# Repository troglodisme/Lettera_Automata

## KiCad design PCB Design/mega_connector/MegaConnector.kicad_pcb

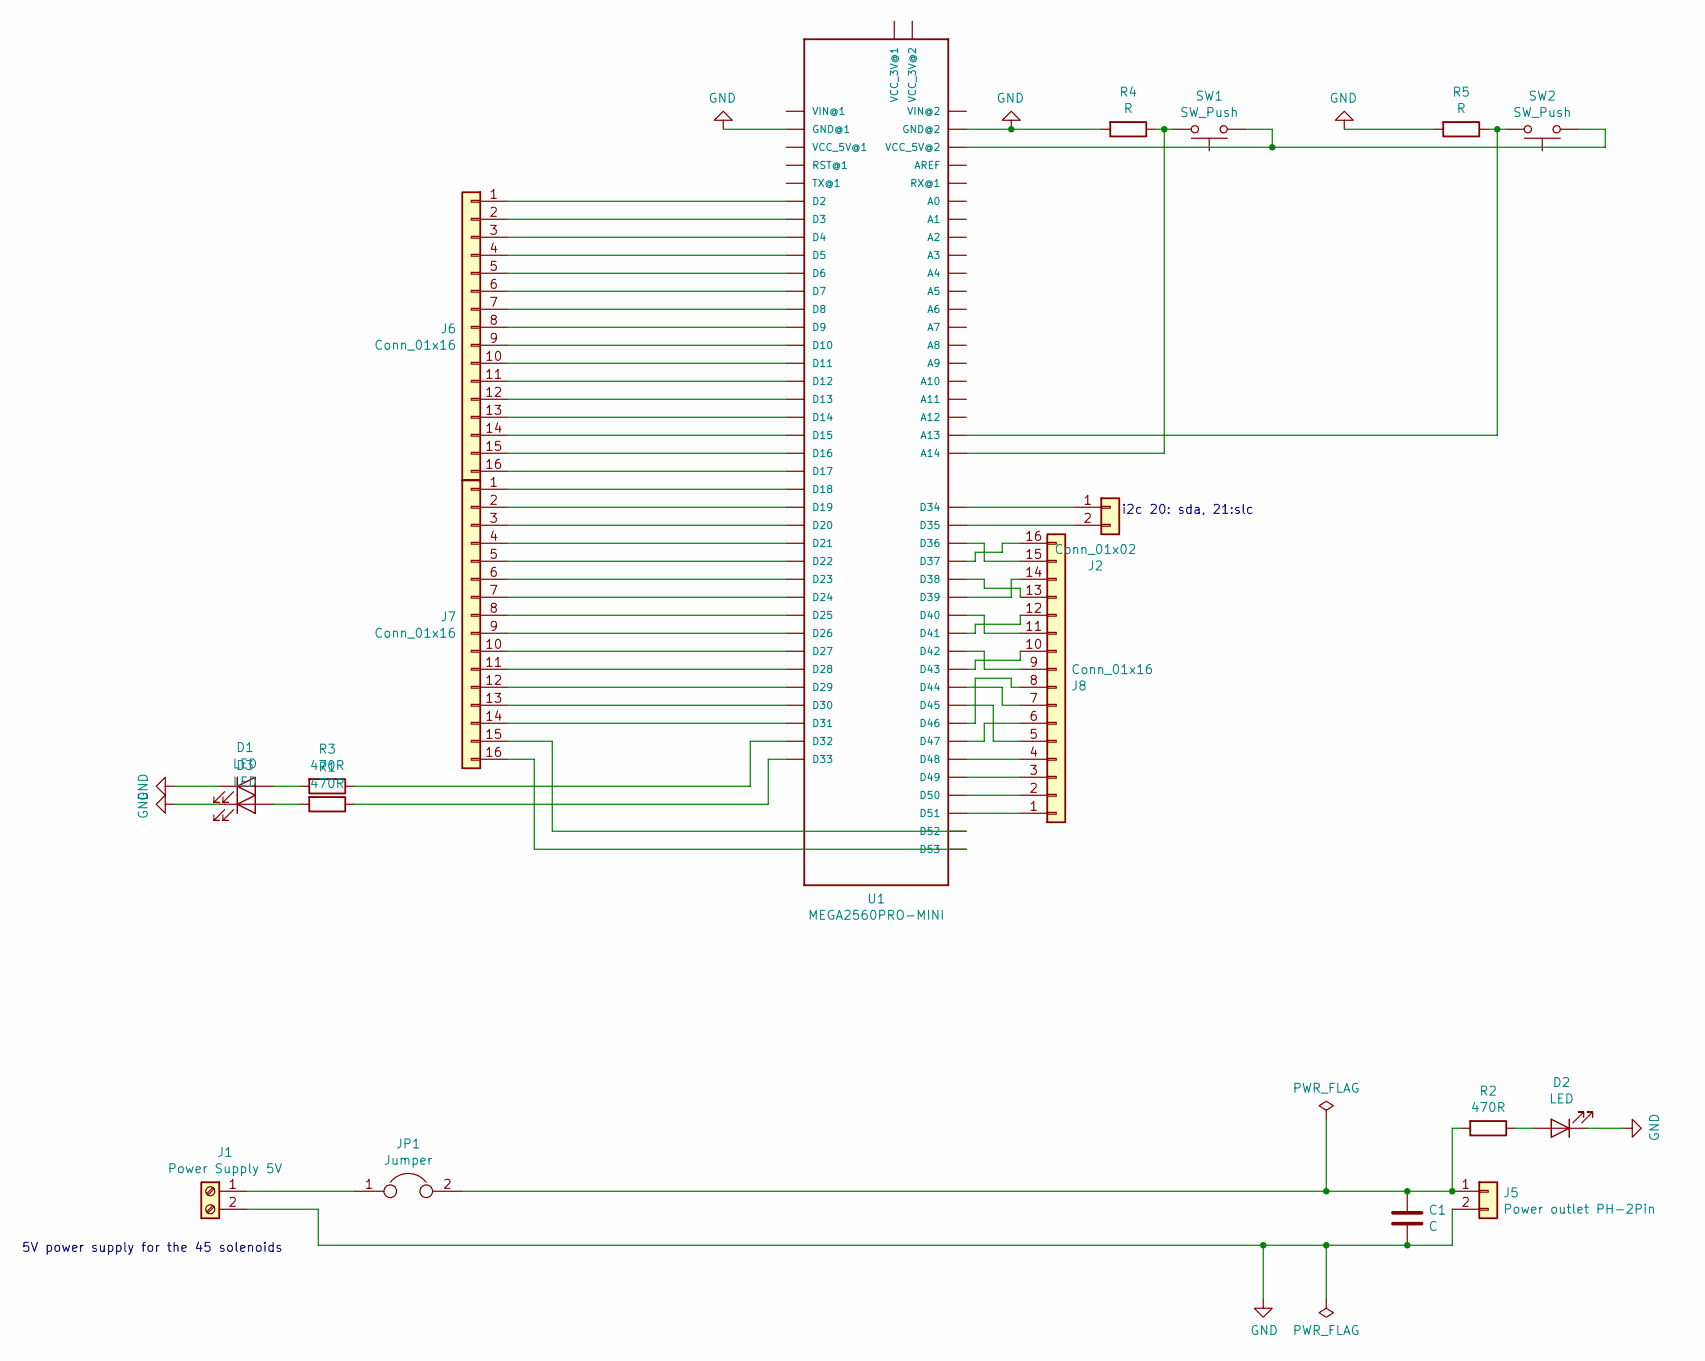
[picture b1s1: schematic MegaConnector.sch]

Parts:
C1: C; C_1206_3216Metric_Pad1.42x1.75mm_HandSolder
D1, D2, D3: LED; LED_D3.0mm
J1: Power Supply 5V; TerminalBlock_TE_282834-2_1x02_P2.54mm_Horizontal
J2: Conn_01x02; PinHeader_1x02_P2.54mm_Vertical
J5: Power outlet PH-2Pin; JST_PH_S2B-PH-K_1x02_P2.00mm_Horizontal
J6, J7, J8: Conn_01x16; IDC-Header_2x08_P2.54mm_Vertical
JP1: Jumper; PinHeader_1x02_P2.54mm_Vertical
R1, R2, R3: 470R; R_1210_3225Metric_Pad1.42x2.65mm_HandSolder
R4, R5: R; R_1210_3225Metric_Pad1.42x2.65mm_HandSolder
SW1, SW2: SW_Push; SW_PUSH-12mm
U1: MEGA2560PRO-MINI; Mega256ProMini_usb

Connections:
GND: C1.2, D1.1 (K), D2.1 (K), D3.1 (K), J1.2, J5.2, R4.2, R5.2, U1.GND@1, U1.GND@2
unnamed: C1.1, J5.1, JP1.2, R2.2
unnamed: D1.2 (A), R3.2
unnamed: D2.2 (A), R2.1
unnamed: D3.2 (A), R1.2
unnamed: J1.1, JP1.1
unnamed: J2.1, U1.D34
unnamed: J2.2, U1.D35
unnamed: J6.1, U1.D2
unnamed: J6.2, U1.D3
unnamed: J6.3, U1.D4
unnamed: J6.4, U1.D5
unnamed: J6.5, U1.D6
unnamed: J6.6, U1.D7
unnamed: J6.7, U1.D8
unnamed: J6.8, U1.D9
unnamed: J6.9, U1.D10
unnamed: J6.10, U1.D11
unnamed: J6.11, U1.D12
unnamed: J6.12, U1.D13
unnamed: J6.13, U1.D14
unnamed: J6.14, U1.D15
unnamed: J6.15, U1.D16
unnamed: J6.16, U1.D17
unnamed: J7.1, U1.D18
unnamed: J7.2, U1.D19
unnamed: J7.3, U1.D20
unnamed: J7.4, U1.D21
unnamed: J7.5, U1.D22
unnamed: J7.6, U1.D23
unnamed: J7.7, U1.D24
unnamed: J7.8, U1.D25
unnamed: J7.9, U1.D26
unnamed: J7.10, U1.D27
unnamed: J7.11, U1.D28
unnamed: J7.12, U1.D29
unnamed: J7.13, U1.D30
unnamed: J7.14, U1.D31
unnamed: J7.15, U1.D52
unnamed: J7.16, U1.D53
unnamed: J8.1, U1.D51
unnamed: J8.2, U1.D50
unnamed: J8.3, U1.D49
unnamed: J8.4, U1.D48
unnamed: J8.5, U1.D45
unnamed: J8.6, U1.D47
unnamed: J8.7, U1.D44
unnamed: J8.8, U1.D46
unnamed: J8.9, U1.D42
unnamed: J8.10, U1.D43
unnamed: J8.11, U1.D40
unnamed: J8.12, U1.D41
unnamed: J8.13, U1.D38
unnamed: J8.14, U1.D39
unnamed: J8.15, U1.D36
unnamed: J8.16, U1.D37
unnamed: R1.1, U1.D33
unnamed: R3.1, U1.D32
unnamed: R4.1, SW1.2, U1.A14
unnamed: R5.1, SW2.2, U1.A13
unnamed: SW1.1, SW2.1, U1.VCC_5V@2

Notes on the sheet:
5V power supply for the 45 solenoids
i2c 20: sda, 21:slc

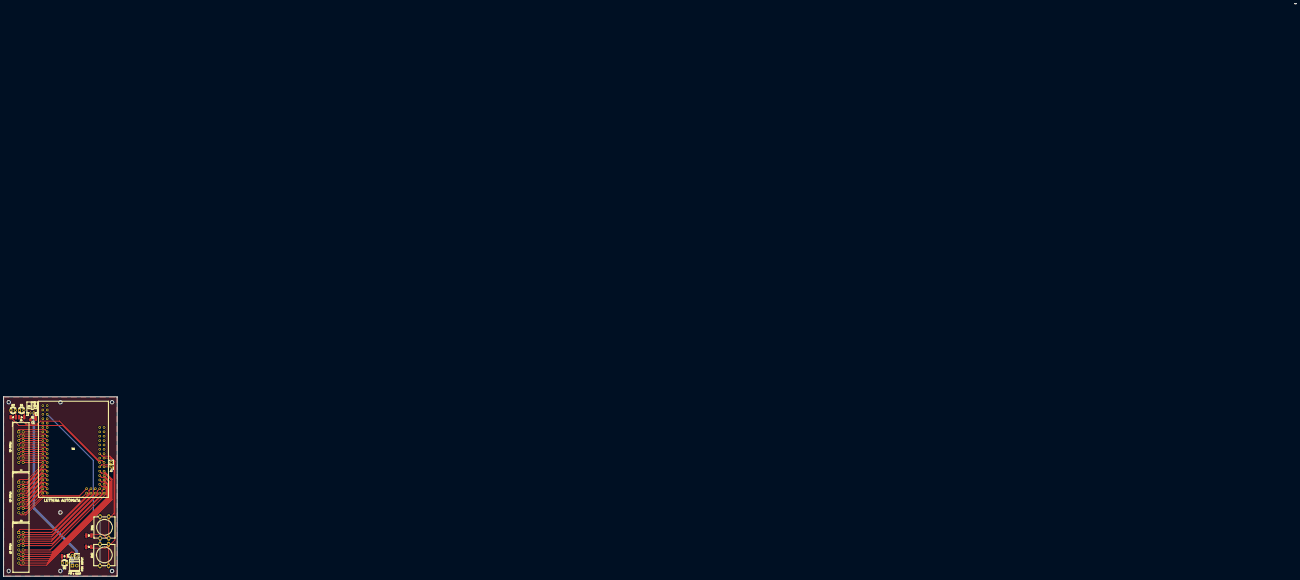
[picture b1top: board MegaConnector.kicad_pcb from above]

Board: 2 copper layers, 66.0 x 104.1 mm, 19 parts (0 on the bottom side), 61 nets.

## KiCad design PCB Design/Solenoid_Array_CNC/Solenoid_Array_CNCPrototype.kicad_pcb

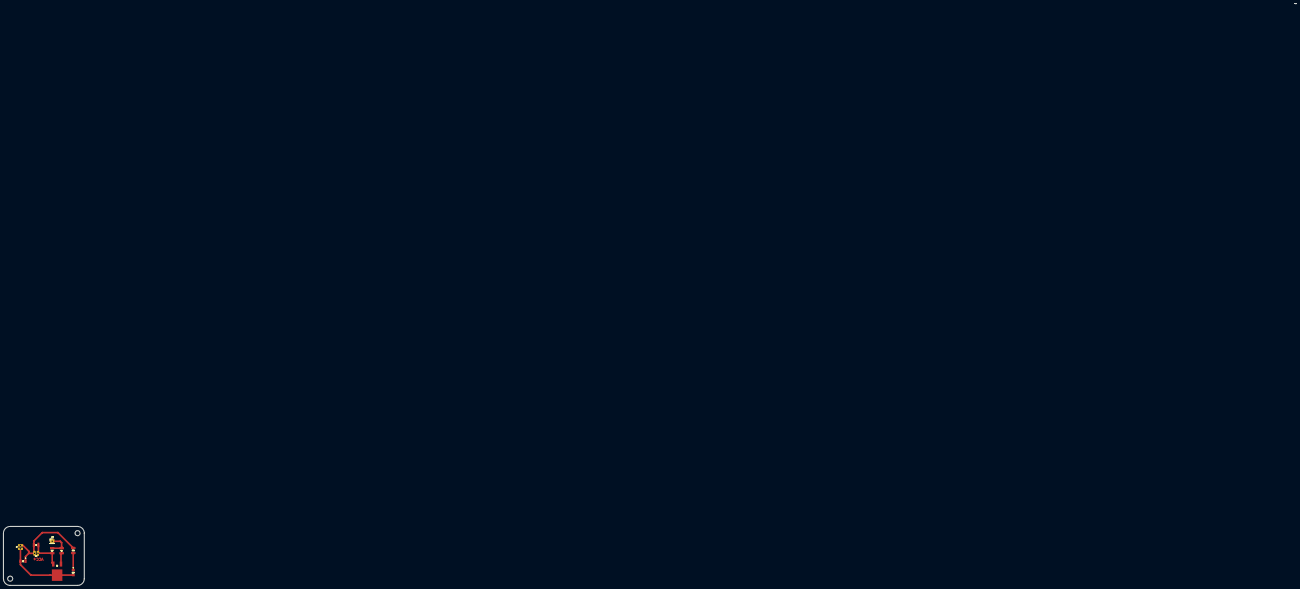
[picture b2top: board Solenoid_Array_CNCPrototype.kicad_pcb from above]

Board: 2 copper layers, 48.0 x 35.0 mm, 10 parts (0 on the bottom side), 6 nets.

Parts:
C1: EMK325ABJ107MM-T; CAPC3225X270N
D1: SD1206S040S2R0
D16: IN-S126AT5UW
J1: Conn_01x02; JST_PH_S2B-PH-K_1x02_P2.00mm_Horizontal_noSilkScreen
J3: Conn_01x01; PinHeader_1x01_P2.54mm_Vertical
J16: Power Daisy Chain_input; JST_PH_S2B-PH-K_1x02_P2.00mm_Horizontal_noSilkScreen
Q1: AOD508
R1: 150R; R_1210_3225Metric_Pad1.42x2.65mm_HandSolder
R17: 100K; R_1210_3225Metric_Pad1.42x2.65mm_HandSolder
R32: 470R; R_1210_3225Metric_Pad1.42x2.65mm_HandSolder

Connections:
+5V: C1.1, D1.1, J1.1, J16.1, R32.2
GND: C1.2, J16.2, Q1.3, R17.2
unnamed: D1.2, D16.1, J1.2, Q1.2
unnamed: D16.2, R32.1
unnamed: J3.1, R1.1, R17.1
unnamed: Q1.1, R1.2

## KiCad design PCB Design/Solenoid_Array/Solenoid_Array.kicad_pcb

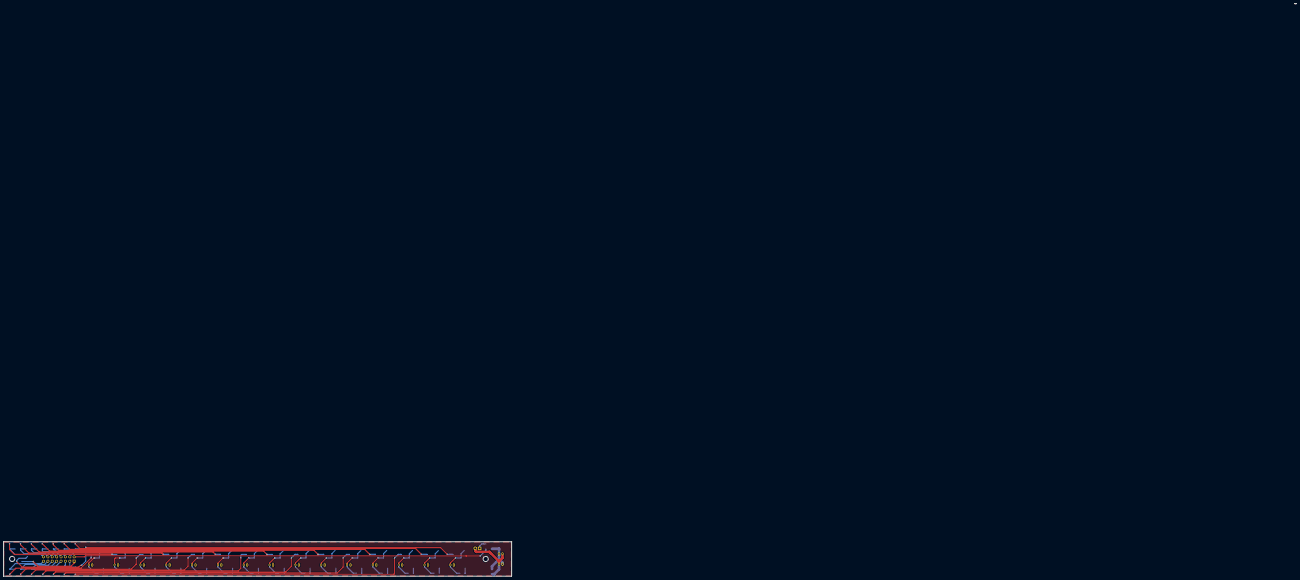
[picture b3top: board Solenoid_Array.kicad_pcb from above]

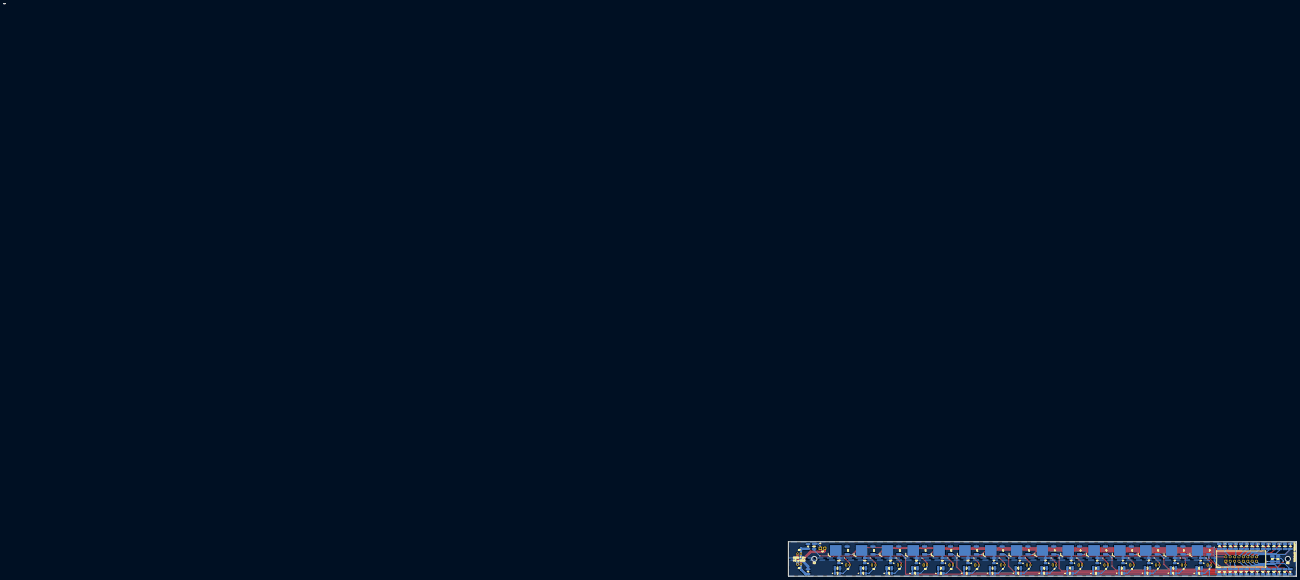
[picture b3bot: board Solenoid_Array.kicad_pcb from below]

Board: 2 copper layers, 295.0 x 20.0 mm, 112 parts (112 on the bottom side), 64 nets.

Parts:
C1, C2: EMK325ABJ107MM-T; CAPC3225X270N
D1, D2, D3, D4, D5, D6, D7, D8, D9, D10, D11, D12, D13, D14, D15: SD1206S040S2R0
D16, D17, D18, D19, D20, D21, D22, D23, D24, D25, D26, D27, D28, D29, D30: LED IN-S126AT5UW; IN-S126AT5UW
J1, J2, J3, J4, J5, J6, J7, J8, J9, J10, J11, J12, J13, J14, J15: Conn_01x02; JST_PH_S2B-PH-K_1x02_P2.00mm_Horizontal_noSilkScreen
J16: Power Daisy Chain_input; JST_PH_S2B-PH-K_1x02_P2.00mm_Horizontal_noSilkScreen
J17: Power Daisy Chain_Output; JST_PH_S2B-PH-K_1x02_P2.00mm_Horizontal_noSilkScreen
J18: Arduino Pins; IDC-Header_2x08_P2.54mm_Vertical_ReversePinNumbers
J19: Screw_Terminal_01x02; TerminalBlock_TE_282834-2_1x02_P2.54mm_Horizontal
Q1, Q2, Q3, Q4, Q5, Q6, Q7, Q8, Q9, Q10, Q11, Q12, Q13, Q14, Q15: TO252 (DPAK); AOD508_GA
R1, R2, R3, R4, R5, R6, R7, R8, R9, R10, R11, R12, R13, R14, R15, R16: 150R; R_1210_3225Metric_Pad1.42x2.65mm_HandSolder
R17, R18, R19, R20, R21, R22, R23, R24, R25, R26, R27, R28, R29, R30, R31: 100K; R_1210_3225Metric_Pad1.42x2.65mm_HandSolder
R32, R33, R34, R35, R36, R37, R38, R39, R40, R41, R42, R43, R44, R45, R46: 470R; R_1210_3225Metric_Pad1.42x2.65mm_HandSolder

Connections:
+5V: C1.1, C2.2, D1.1, D2.1, D3.1, D4.1, D5.1, D6.1, D7.1, D8.1, D9.1, D10.1, D11.1, D12.1, D13.1, D14.1, D15.1, J1.1, J2.1, J3.1, J4.1, J5.1, J6.1, J7.1, J8.1, J9.1, J10.1, J11.1, J12.1, J13.1, J14.1, J15.1, J16.1, J17.1, R32.2, R33.2, R34.2, R35.2, R36.2, R37.2, R38.2, R39.2, R40.2, R41.2, R42.2, R43.2, R44.2, R45.2, R46.2
GND: C1.2, C2.1, J16.2, J17.2, J19.2, Q1.3, Q2.3, Q3.3, Q4.3, Q5.3, Q6.3, Q7.3, Q8.3, Q9.3, Q10.3, Q11.3, Q12.3, Q13.3, Q14.3, Q15.3, R17.2, R18.2, R19.2, R20.2, R21.2, R22.2, R23.2, R24.2, R25.2, R26.2, R27.2, R28.2, R29.2, R30.2, R31.2
unnamed: D1.2, D16.1, J1.2, Q1.2
unnamed: D10.2, D25.1, J10.2, Q10.2
unnamed: D11.2, D26.1, J11.2, Q11.2
unnamed: D12.2, D27.1, J12.2, Q12.2
unnamed: D13.2, D28.1, J13.2, Q13.2
unnamed: D14.2, D29.1, J14.2, Q14.2
unnamed: D15.2, D30.1, J15.2, Q15.2
unnamed: D16.2, R32.1
unnamed: D2.2, D17.1, J2.2, Q2.2
unnamed: D17.2, R33.1
unnamed: D3.2, D18.1, J3.2, Q3.2
unnamed: D18.2, R34.1
unnamed: D4.2, D19.1, J4.2, Q4.2
unnamed: D19.2, R35.1
unnamed: D5.2, D20.1, J5.2, Q5.2
unnamed: D20.2, R36.1
unnamed: D6.2, D21.1, J6.2, Q6.2
unnamed: D21.2, R37.1
unnamed: D7.2, D22.1, J7.2, Q7.2
unnamed: D22.2, R38.1
unnamed: D8.2, D23.1, J8.2, Q8.2
unnamed: D23.2, R39.1
unnamed: D9.2, D24.1, J9.2, Q9.2
unnamed: D24.2, R40.1
unnamed: D25.2, R41.1
unnamed: D26.2, R42.1
unnamed: D27.2, R43.1
unnamed: D28.2, R44.1
unnamed: D29.2, R45.1
unnamed: D30.2, R46.1
unnamed: J18.1, R1.1, R17.1
unnamed: J18.2, R2.1, R18.1
unnamed: J18.3, R3.1, R19.1
unnamed: J18.4, R4.1, R20.1
unnamed: J18.5, R5.1, R21.1
unnamed: J18.6, R6.1, R22.1
unnamed: J18.7, R7.1, R23.1
unnamed: J18.8, R8.1, R24.1
unnamed: J18.9, R9.1, R25.1
unnamed: J18.10, R10.1, R26.1
unnamed: J18.11, R11.1, R27.1
unnamed: J18.12, R12.1, R28.1
unnamed: J18.13, R13.1, R29.1
unnamed: J18.14, R14.1, R30.1
unnamed: J18.15, R15.1, R31.1
unnamed: J18.16, R16.1
unnamed: J19.1, R16.2
unnamed: Q1.1, R1.2
unnamed: Q2.1, R2.2
unnamed: Q3.1, R3.2
unnamed: Q4.1, R4.2
unnamed: Q5.1, R5.2
unnamed: Q6.1, R6.2
unnamed: Q7.1, R7.2
unnamed: Q8.1, R8.2
unnamed: Q9.1, R9.2
unnamed: Q10.1, R10.2
unnamed: Q11.1, R11.2
unnamed: Q12.1, R12.2
unnamed: Q13.1, R13.2
unnamed: Q14.1, R14.2
unnamed: Q15.1, R15.2

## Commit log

2020-05-14 All schematic symbols selected and matched with BOM components
2020-05-15 Added silkscreen polarity and naming
2020-05-15 Repositioned Q1-15
2020-05-22 CNC Prototype
2020-05-23 revised connectors placement
2020-10-04 added software folder
2020-10-04 readme
2020-10-04 reorganised repo and moved connector pcb
2020-10-04 try again
2020-10-04 fixed led wire missing
2020-12-04 working demo
